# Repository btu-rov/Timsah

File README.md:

# Timsah
This is Open Source ROV project which is made by Bursa Technical University ROV Team.

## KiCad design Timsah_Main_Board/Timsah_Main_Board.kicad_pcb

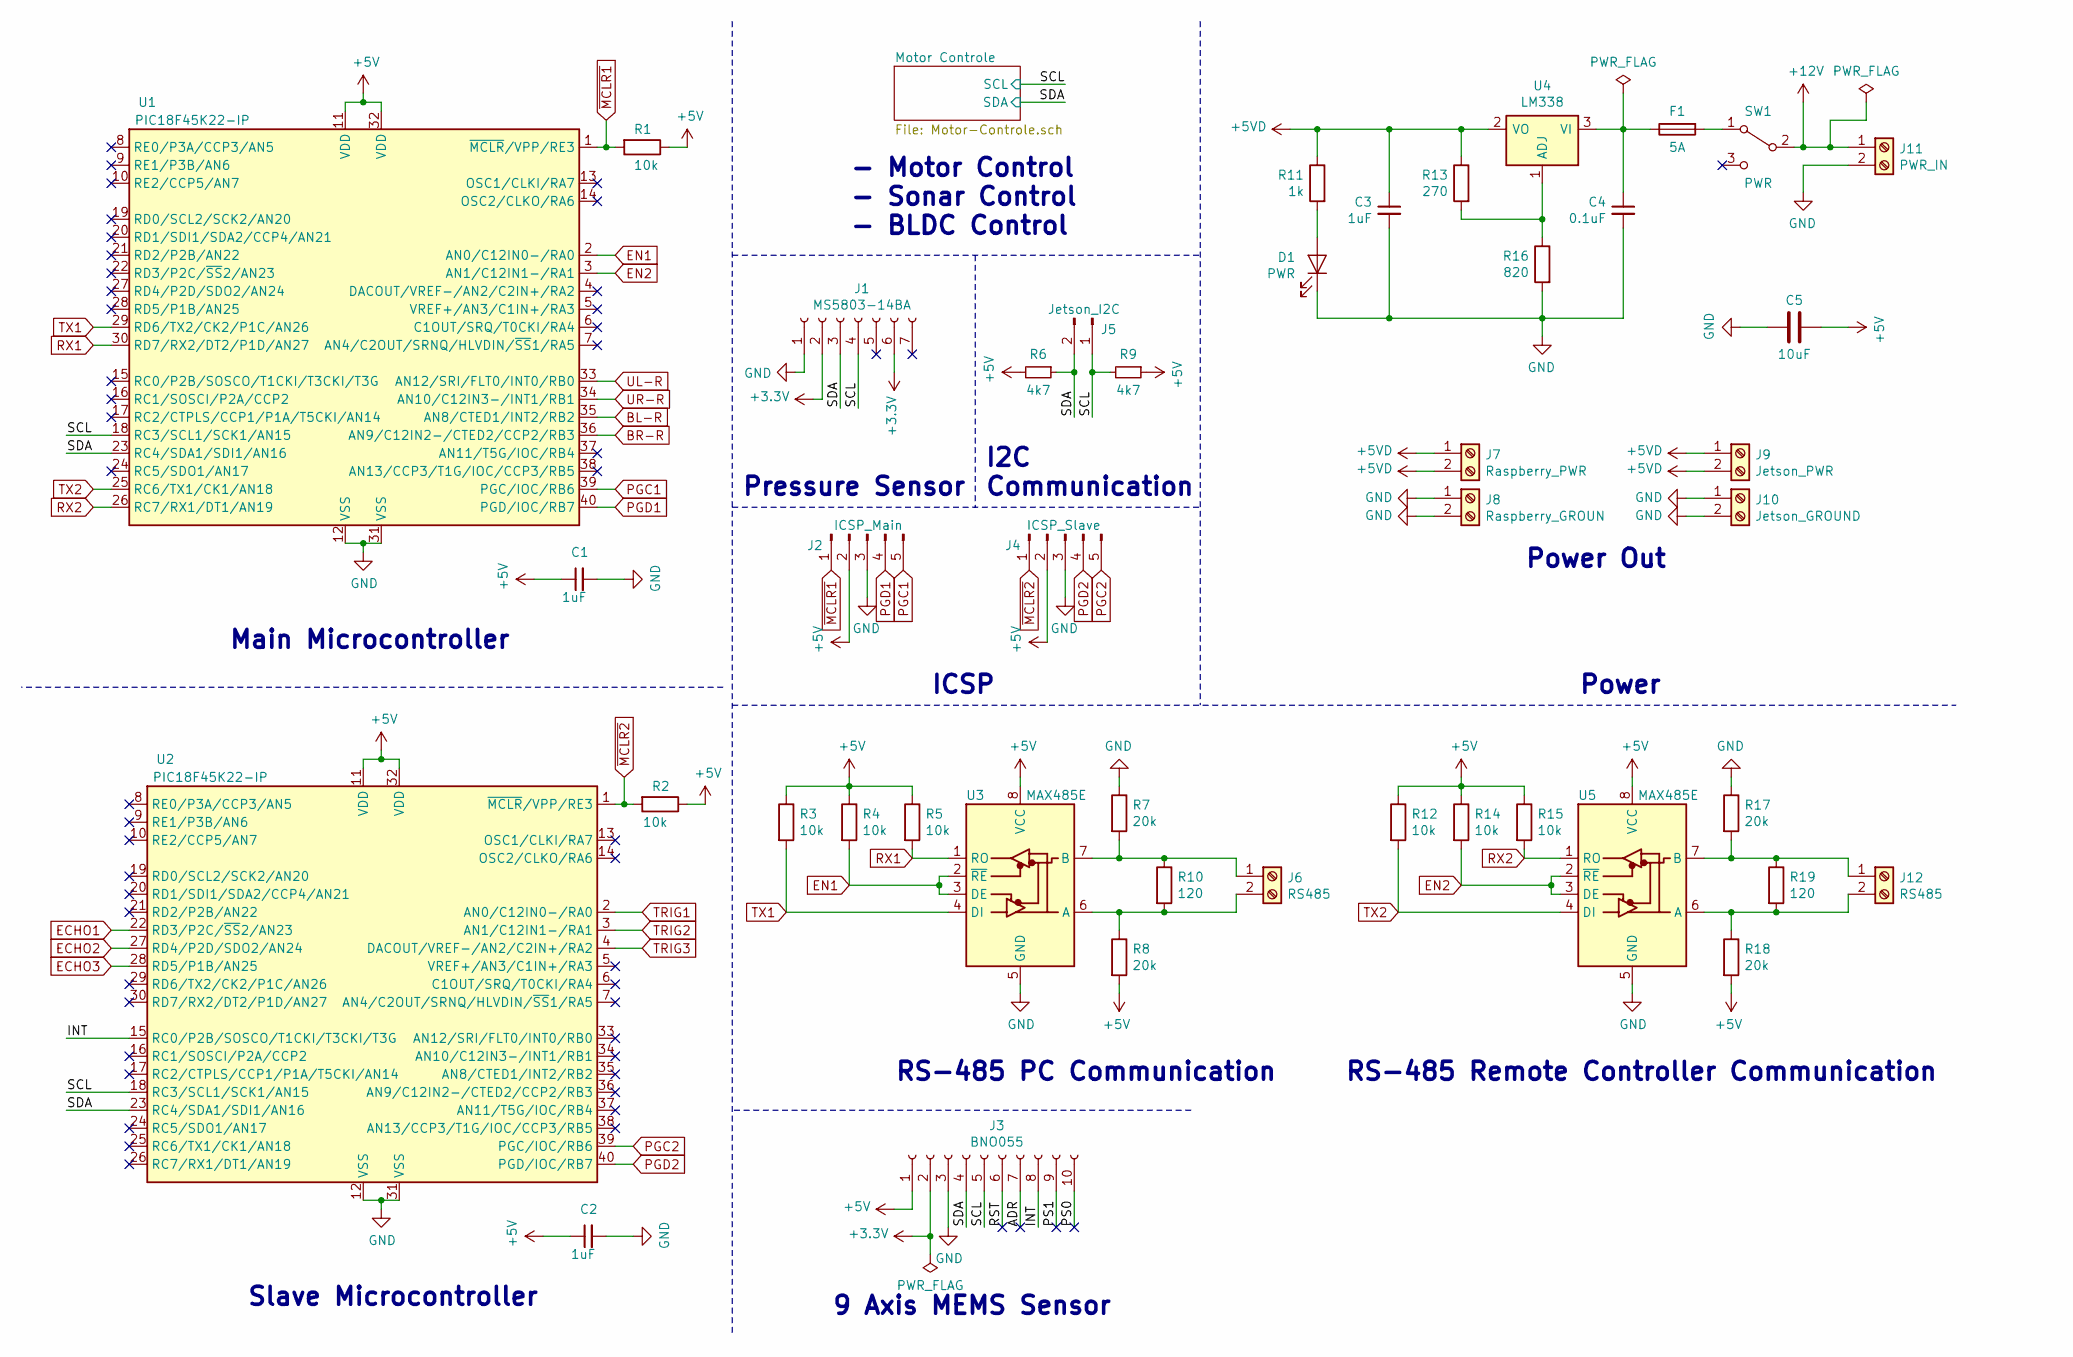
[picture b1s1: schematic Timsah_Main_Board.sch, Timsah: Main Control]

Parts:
C1, C2, C3: 1uF; C_0805_2012Metric_Pad1.15x1.40mm_HandSolder
C4: 0.1uF; C_0805_2012Metric_Pad1.15x1.40mm_HandSolder
C5: 10uF; C_0805_2012Metric_Pad1.15x1.40mm_HandSolder
D1: PWR; LED_0805_2012Metric_Pad1.15x1.40mm_HandSolder
F1: 5A; Fuseholder_23x9x10mm
J1: MS5803-14BA; PinSocket_1x07_P2.54mm_Vertical
J2: ICSP_Main; PinSocket_1x05_P2.54mm_Vertical
J3: BNO055; BNO055-Module_Adafruit
J4: ICSP_Slave; PinSocket_1x05_P2.54mm_Vertical
J5: Jetson_I2C; PinHeader_1x02_P2.54mm_Vertical
J6, J12: RS485; TerminalBlock_4Ucon_1x02_P3.50mm_Vertical
J7: Raspberry_PWR; TerminalBlock_4Ucon_1x02_P3.50mm_Vertical
J8: Raspberry_GROUN; TerminalBlock_4Ucon_1x02_P3.50mm_Vertical
J9: Jetson_PWR; TerminalBlock_4Ucon_1x02_P3.50mm_Vertical
J10: Jetson_GROUND; TerminalBlock_4Ucon_1x02_P3.50mm_Vertical
J11: PWR_IN; TerminalBlock_bornier-2_P5.08mm
R1, R2, R3, R4, R5, R12, R14, R15: 10k; R_0805_2012Metric_Pad1.15x1.40mm_HandSolder
R6, R9: 4k7; R_0805_2012Metric_Pad1.15x1.40mm_HandSolder
R7, R8, R17, R18: 20k; R_0805_2012Metric_Pad1.15x1.40mm_HandSolder
R10, R19: 120; R_Axial_DIN0207_L6.3mm_D2.5mm_P10.16mm_Horizontal
R11: 1k; R_0805_2012Metric_Pad1.15x1.40mm_HandSolder
R13: 270; R_Axial_DIN0207_L6.3mm_D2.5mm_P10.16mm_Horizontal
R16: 820; R_Axial_DIN0207_L6.3mm_D2.5mm_P10.16mm_Horizontal
SW1: PWR; SW_Slide_1P2T_0.105pitch
U1, U2: PIC18F45K22-IP; DIP-40_W15.24mm_Socket
U3, U5: MAX485E; DIP-8_W7.62mm_Socket
U4: LM338; TO-3

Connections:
+3V3: J1.2, J1.6, J3.2
+5VD: C3.1, J7.1, J7.2, J9.1, J9.2, R11.1, R13.1, U4.2 (VO)
+12V: J11.1, SW1.2 (B); also elsewhere on the board
/ADR: J3.7
/INT: J3.8, U2.15 (RC0/P2B/SOSCO/T1CKI/T3CKI/T3G)
/PS0: J3.10
/PS1: J3.9
/RST: J3.6
/SCL: J1.4, J3.5, J5.1, R9.2, U1.18 (RC3/SCL1/SCK1/AN15), U2.18 (RC3/SCL1/SCK1/AN15); also elsewhere on the board
/SDA: J1.3, J3.4, J5.2, R6.1, U1.23 (RC4/SDA1/SDI1/AN16), U2.23 (RC4/SDA1/SDI1/AN16); also elsewhere on the board
BEC: C1.1, C2.1, C5.1, J2.2, J3.1, J4.2, R1.1, R2.1, R3.1, R4.1, R5.1, R6.2, R8.2, R9.1, R12.1, R14.1, R15.1, R18.2, U1.11 (VDD), U1.32 (VDD), U2.11 (VDD), U2.32 (VDD), U3.8 (VCC), U5.8 (VCC); also elsewhere on the board
BL-R: U1.35 (AN8/CTED1/INT2/RB2); also elsewhere on the board
BR-R: U1.36 (AN9/C12IN2-/CTED2/CCP2/RB3); also elsewhere on the board
ECHO1: U2.22 (RD3/P2C/~SS~2/AN23); also elsewhere on the board
ECHO2: U2.27 (RD4/P2D/SDO2/AN24); also elsewhere on the board
ECHO3: U2.28 (RD5/P1B/AN25); also elsewhere on the board
EN1: R4.2, U1.2 (AN0/C12IN0-/RA0), U3.2 (~RE), U3.3 (DE)
EN2: R14.2, U1.3 (AN1/C12IN1-/RA1), U5.2 (~RE), U5.3 (DE)
GND: C1.2, C2.2, C3.2, C4.2, C5.2, D1.1 (K), J1.1, J2.3, J3.3, J4.3, J8.1, J8.2, J10.1, J10.2, J11.2, R7.1, R16.2, R17.1, U1.12 (VSS), U1.31 (VSS), U2.12 (VSS), U2.31 (VSS), U3.5 (GND), U5.5 (GND); also elsewhere on the board
unnamed: C4.1, F1.1, U4.3 (VI)
unnamed: D1.2 (A), R11.2
unnamed: F1.2, SW1.1 (A)
unnamed: J6.1, R7.2, R10.1, U3.7 (B)
unnamed: J6.2, R8.1, R10.2, U3.6 (A)
unnamed: J12.1, R17.2, R19.1, U5.7 (B)
unnamed: J12.2, R18.1, R19.2, U5.6 (A)
unnamed: R13.2, R16.1, U4.1 (ADJ)
PGC1: J2.5, U1.39 (PGC/IOC/RB6)
PGC2: J4.5, U2.39 (PGC/IOC/RB6)
PGD1: J2.4, U1.40 (PGD/IOC/RB7)
PGD2: J4.4, U2.40 (PGD/IOC/RB7)
RX1: R5.2, U1.30 (RD7/RX2/DT2/P1D/AN27), U3.1 (RO)
RX2: R15.2, U1.26 (RC7/RX1/DT1/AN19), U5.1 (RO)
TRIG1: U2.2 (AN0/C12IN0-/RA0); also elsewhere on the board
TRIG2: U2.3 (AN1/C12IN1-/RA1); also elsewhere on the board
TRIG3: U2.4 (DACOUT/VREF-/AN2/C2IN+/RA2); also elsewhere on the board
TX1: R3.2, U1.29 (RD6/TX2/CK2/P1C/AN26), U3.4 (DI)
TX2: R12.2, U1.25 (RC6/TX1/CK1/AN18), U5.4 (DI)
UL-R: U1.33 (AN12/SRI/FLT0/INT0/RB0); also elsewhere on the board
UR-R: U1.34 (AN10/C12IN3-/INT1/RB1); also elsewhere on the board
~MCLR1: J2.1, R1.2, U1.1 (~MCLR~/VPP/RE3)
~MCLR2: J4.1, R2.2, U2.1 (~MCLR~/VPP/RE3)

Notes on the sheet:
Power
9 Axis MEMS Sensor
RS-485 Remote Controller Communication
Slave Microcontroller
Main Microcontroller
Pressure Sensor
ICSP
Power Out
I2C Communication
RS-485 PC Communication
- Motor Control - Sonar Control - BLDC Control

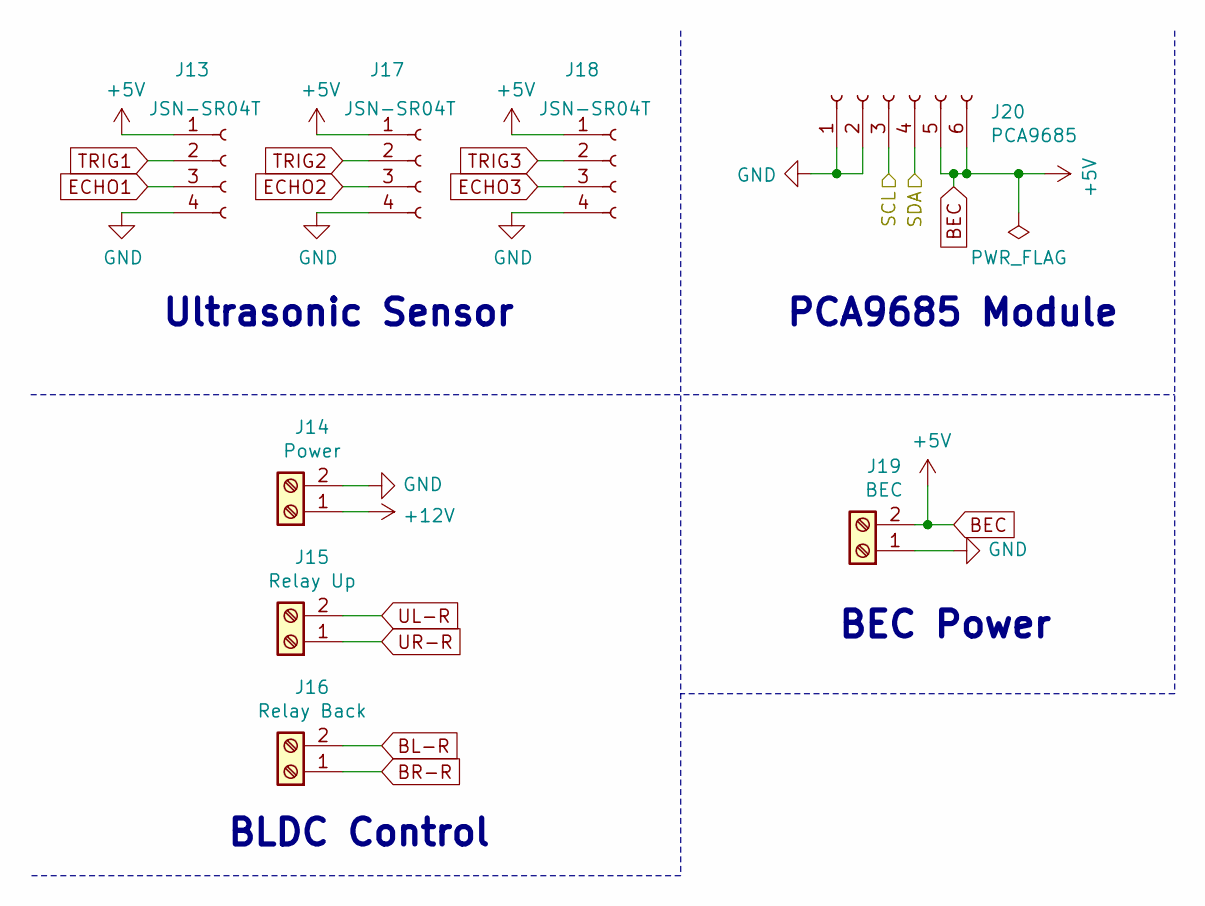
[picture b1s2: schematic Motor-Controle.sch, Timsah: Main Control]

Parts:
J13, J17, J18: JSN-SR04T; PinSocket_1x04_P2.54mm_Vertical
J14: Power; TerminalBlock_bornier-2_P5.08mm
J15: Relay Up; PinSocket_1x02_P2.54mm_Vertical
J16: Relay Back; PinSocket_1x02_P2.54mm_Vertical
J19: BEC; TerminalBlock_4Ucon_1x02_P3.50mm_Vertical
J20: PCA9685; PinSocket_1x06_P2.54mm_Vertical

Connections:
+12V: J14.1; also elsewhere on the board
/SCL: J20.3; also elsewhere on the board
/SDA: J20.4; also elsewhere on the board
BEC: J13.1, J17.1, J18.1, J19.2, J20.5, J20.6; also elsewhere on the board
BL-R: J16.2; also elsewhere on the board
BR-R: J16.1; also elsewhere on the board
ECHO1: J13.3; also elsewhere on the board
ECHO2: J17.3; also elsewhere on the board
ECHO3: J18.3; also elsewhere on the board
GND: J13.4, J14.2, J17.4, J18.4, J19.1, J20.1, J20.2; also elsewhere on the board
TRIG1: J13.2; also elsewhere on the board
TRIG2: J17.2; also elsewhere on the board
TRIG3: J18.2; also elsewhere on the board
UL-R: J15.2; also elsewhere on the board
UR-R: J15.1; also elsewhere on the board

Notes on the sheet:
BLDC Control
Ultrasonic Sensor
PCA9685 Module
BEC Power

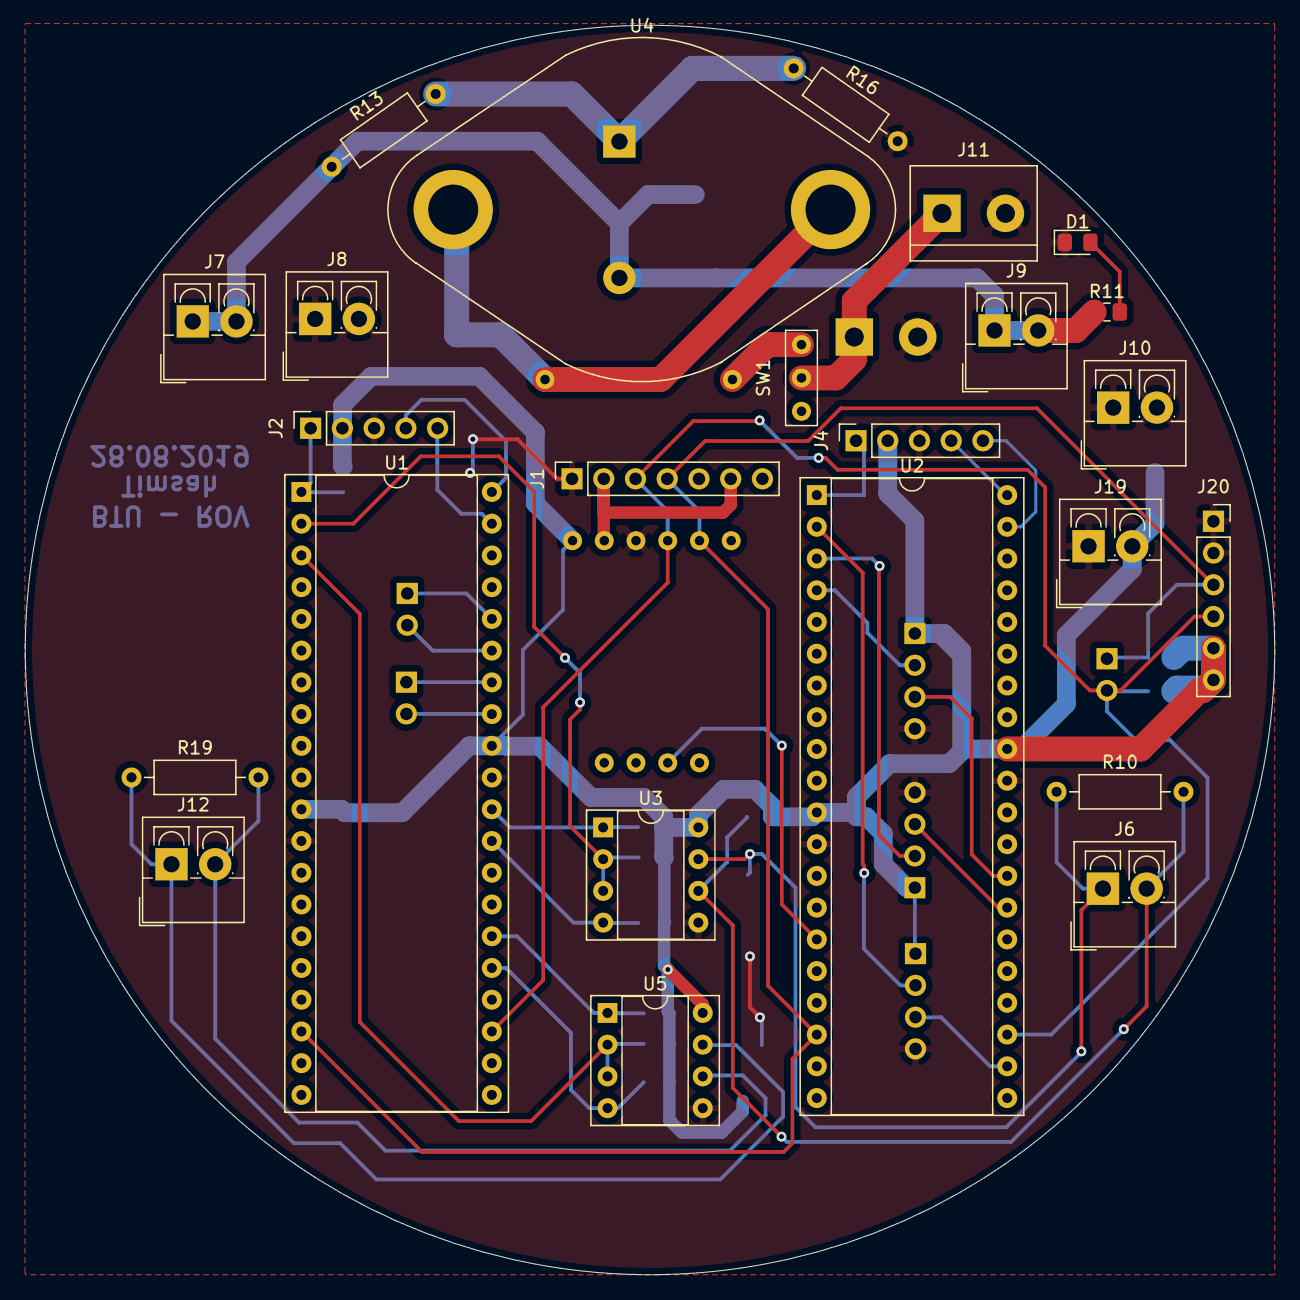
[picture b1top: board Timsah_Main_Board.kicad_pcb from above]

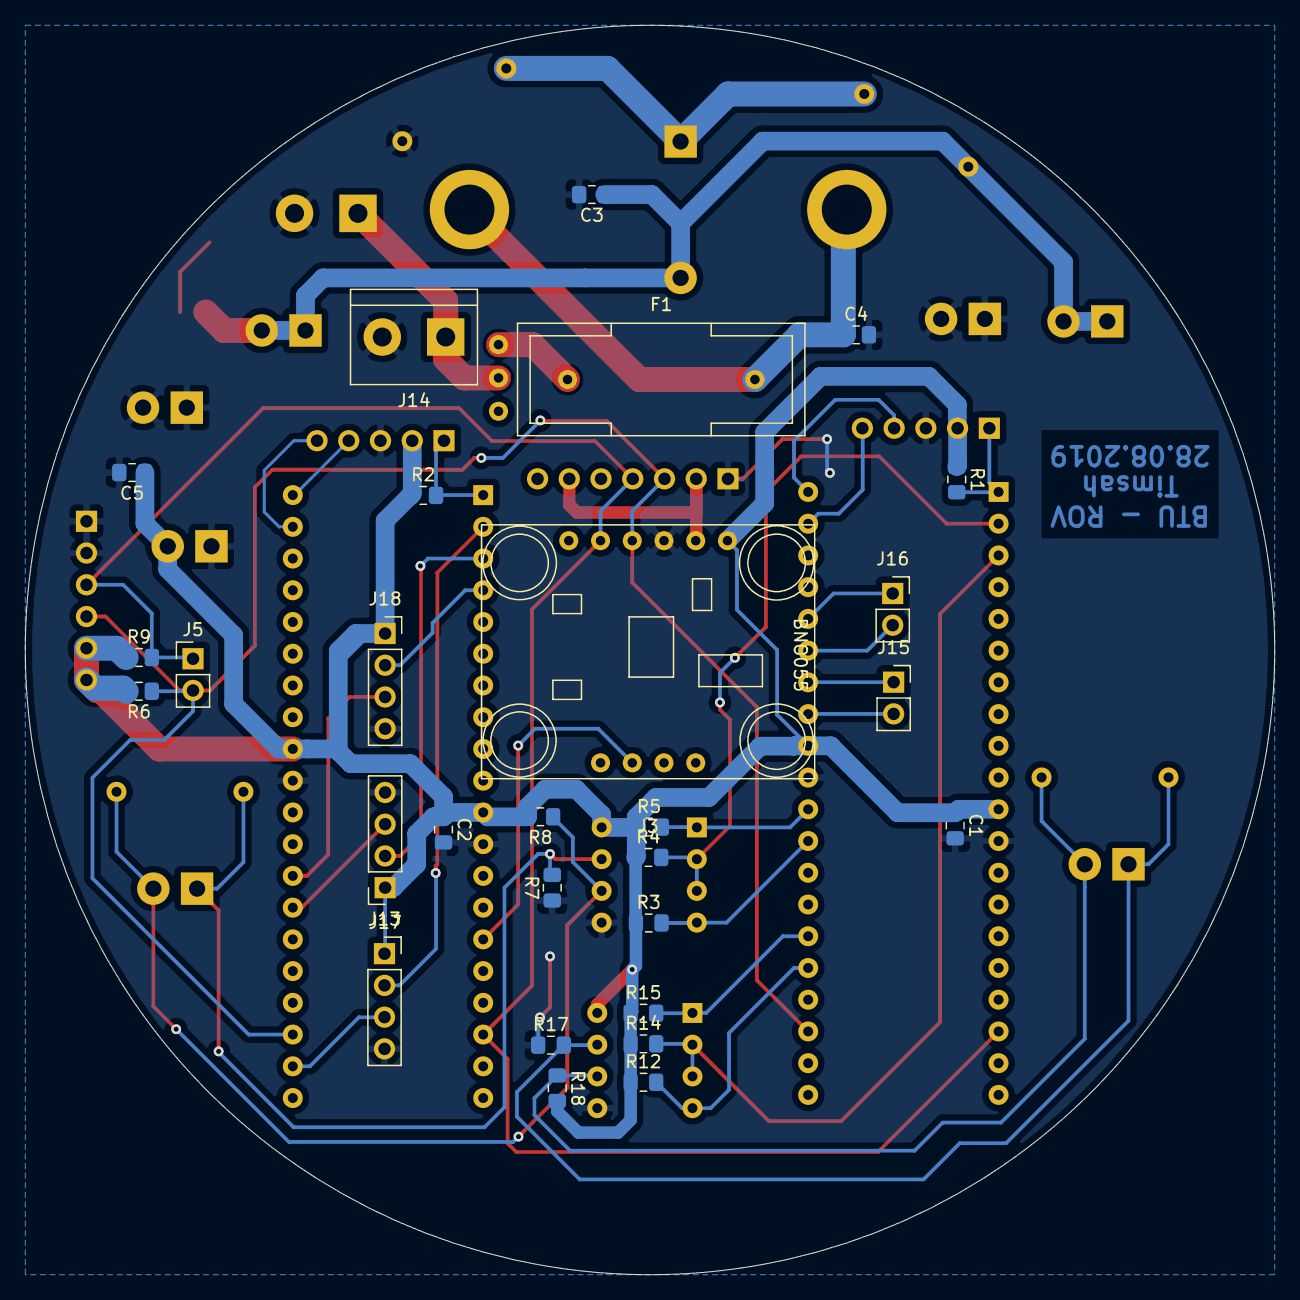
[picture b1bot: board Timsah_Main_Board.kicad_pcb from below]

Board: 2 copper layers, 100.0 x 100.0 mm, 52 parts (28 on the bottom side), 38 nets.

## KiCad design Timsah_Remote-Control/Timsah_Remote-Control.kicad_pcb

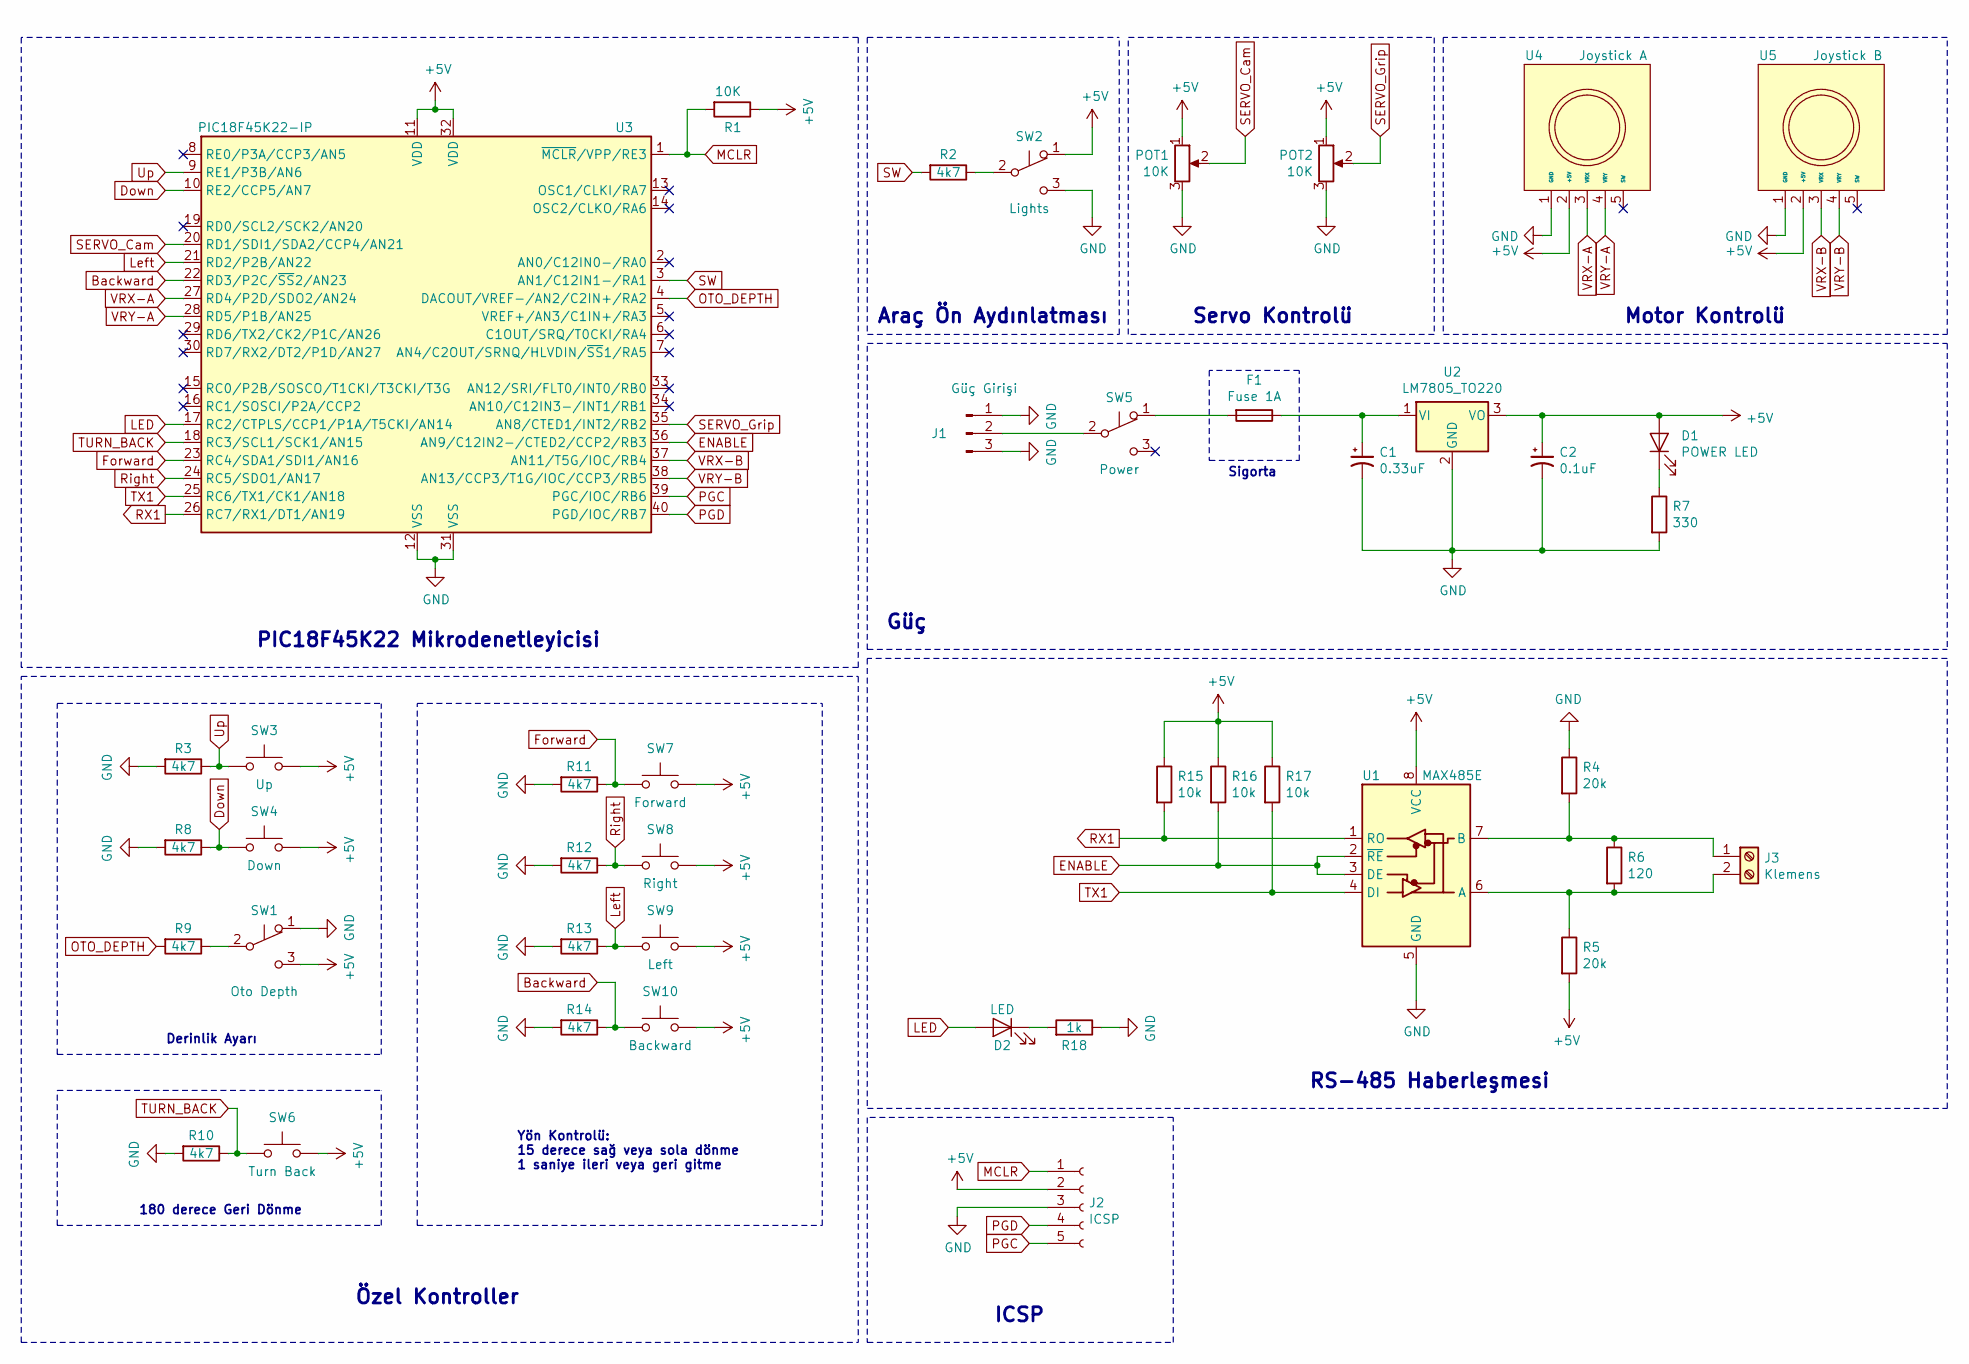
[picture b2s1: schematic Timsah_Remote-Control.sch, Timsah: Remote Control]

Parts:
C1: 0.33uF; C_Radial_D5.0mm_H7.0mm_P2.00mm
C2: 0.1uF; C_Radial_D5.0mm_H7.0mm_P2.00mm
D1: POWER LED; LED_D5.0mm
D2: LED; LED_D5.0mm
F1: Fuse 1A; Fuseholder_23x9x10mm
J1: Güç Girişi; PinHeader_1x03_P2.54mm_Vertical
J2: ICSP; PinHeader_1x05_P2.54mm_Vertical
J3: Klemens; TerminalBlock_4Ucon_1x02_P3.50mm_Vertical
POT1, POT2: 10K; Potentiometer_Lineer-B503
R1: 10K; R_Axial_DIN0207_L6.3mm_D2.5mm_P10.16mm_Horizontal
R2, R3, R8, R9, R10, R11, R12, R13, R14: 4k7; R_Axial_DIN0207_L6.3mm_D2.5mm_P10.16mm_Horizontal
R4, R5: 20k; R_Axial_DIN0207_L6.3mm_D2.5mm_P10.16mm_Horizontal
R6: 120; R_Axial_DIN0207_L6.3mm_D2.5mm_P10.16mm_Horizontal
R7: 330; R_Axial_DIN0207_L6.3mm_D2.5mm_P10.16mm_Horizontal
R15, R16, R17: 10k; R_Axial_DIN0207_L6.3mm_D2.5mm_P10.16mm_Horizontal
R18: 1k; R_Axial_DIN0207_L6.3mm_D2.5mm_P10.16mm_Horizontal
SW1: Oto Depth; SW_Slide_1P2T_0.105pitch
SW2: Lights; SW_Slide_1P2T_0.105pitch
SW3: Up; SW_PUSH_6mm_H5mm
SW4: Down; SW_PUSH_6mm_H5mm
SW5: Power; SW_Slide_1P2T_0.105pitch
SW6: Turn Back; SW_PUSH_6mm_H5mm
SW7: Forward; SW_PUSH_6mm_H5mm
SW8: Right; SW_PUSH_6mm_H5mm
SW9: Left; SW_PUSH_6mm_H5mm
SW10: Backward; SW_PUSH_6mm_H5mm
U1: MAX485E; DIP-8_W7.62mm_Socket
U2: LM7805_TO220; TO-220-3_Vertical
U3: PIC18F45K22-IP; DIP-40_W15.24mm_Socket
U4: Joystick A; Joystick
U5: Joystick B; Joystick

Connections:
+5V: C2.1, D1.2 (A), J2.2, POT1.1, POT2.1, R1.1, R5.2, R15.1, R16.1, R17.1, SW1.3 (C), SW2.1 (A), SW3.2, SW4.2, SW6.2, SW7.2, SW8.2, SW9.2, SW10.2, U1.8 (VCC), U2.3 (VO), U3.11 (VDD), U3.32 (VDD), U4.2 (+5V), U5.2 (+5V)
Backward: R14.1, SW10.1, U3.22 (RD3/P2C/~SS~2/AN23)
Down: R8.1, SW4.1, U3.10 (RE2/CCP5/AN7)
ENABLE: R16.2, U1.2 (~RE), U1.3 (DE), U3.36 (AN9/C12IN2-/CTED2/CCP2/RB3)
Forward: R11.1, SW7.1, U3.23 (RC4/SDA1/SDI1/AN16)
GND: C1.2, C2.2, J1.1, J1.3, J2.3, POT1.3, POT2.3, R3.2, R4.1, R7.2, R8.2, R10.2, R11.2, R12.2, R13.2, R14.2, R18.1, SW1.1 (A), SW2.3 (C), U1.5 (GND), U2.2 (GND), U3.12 (VSS), U3.31 (VSS), U4.1 (GND), U5.1 (GND)
LED: D2.2 (A), U3.17 (RC2/CTPLS/CCP1/P1A/T5CKI/AN14)
Left: R13.1, SW9.1, U3.21 (RD2/P2B/AN22)
MCLR: J2.1, R1.2, U3.1 (~MCLR~/VPP/RE3)
unnamed: C1.1, F1.1, U2.1 (VI)
unnamed: D1.1 (K), R7.1
unnamed: D2.1 (K), R18.2
unnamed: F1.2, SW5.1 (A)
unnamed: J1.2, SW5.2 (B)
unnamed: J3.1, R4.2, R6.1, U1.7 (B)
unnamed: J3.2, R5.1, R6.2, U1.6 (A)
unnamed: R2.1, SW2.2 (B)
unnamed: R9.1, SW1.2 (B)
OTO_DEPTH: R9.2, U3.4 (DACOUT/VREF-/AN2/C2IN+/RA2)
PGC: J2.5, U3.39 (PGC/IOC/RB6)
PGD: J2.4, U3.40 (PGD/IOC/RB7)
RX1: R15.2, U1.1 (RO), U3.26 (RC7/RX1/DT1/AN19)
Right: R12.1, SW8.1, U3.24 (RC5/SDO1/AN17)
SERVO_Cam: POT1.2, U3.20 (RD1/SDI1/SDA2/CCP4/AN21)
SERVO_Grip: POT2.2, U3.35 (AN8/CTED1/INT2/RB2)
SW: R2.2, U3.3 (AN1/C12IN1-/RA1)
TURN_BACK: R10.1, SW6.1, U3.18 (RC3/SCL1/SCK1/AN15)
TX1: R17.2, U1.4 (DI), U3.25 (RC6/TX1/CK1/AN18)
Up: R3.1, SW3.1, U3.9 (RE1/P3B/AN6)
VRX-A: U3.27 (RD4/P2D/SDO2/AN24), U4.3 (VRX)
VRX-B: U3.37 (AN11/T5G/IOC/RB4), U5.3 (VRX)
VRY-A: U3.28 (RD5/P1B/AN25), U4.4 (VRY)
VRY-B: U3.38 (AN13/CCP3/T1G/IOC/CCP3/RB5), U5.4 (VRY)

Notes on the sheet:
Motor Kontrolü
Servo Kontrolü
Araç Ön Aydınlatması
Güç
RS-485 Haberleşmesi
ICSP
PIC18F45K22 Mikrodenetleyicisi
Sigorta
Derinlik Ayarı
180 derece Geri Dönme
Yön Kontrolü: 15 derece sağ veya sola dönme 1 saniye ileri veya geri gitme
Özel Kontroller

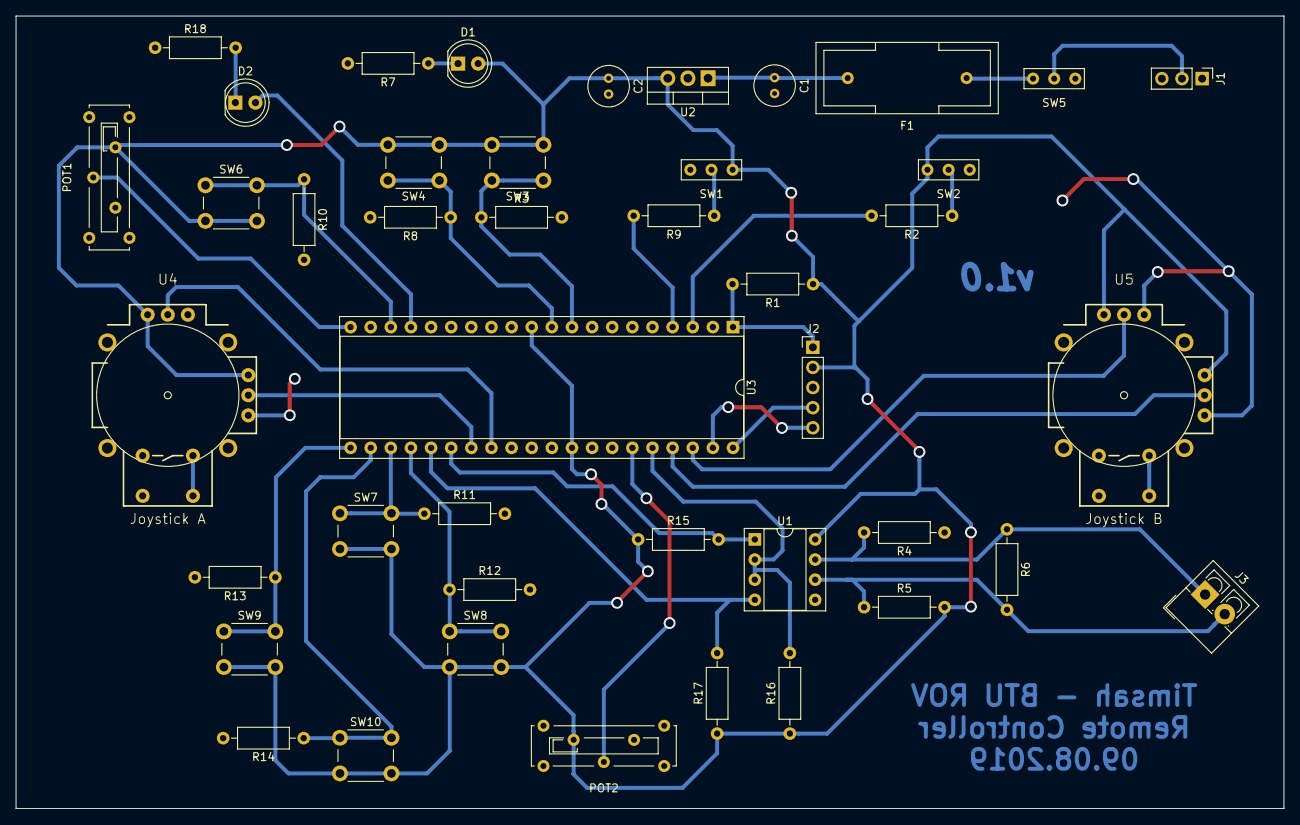
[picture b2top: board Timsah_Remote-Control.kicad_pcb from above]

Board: 2 copper layers, 160.0 x 100.0 mm, 43 parts (0 on the bottom side), 33 nets.

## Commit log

2019-03-24 Timsah GUI initialize.
2019-03-24 Data read protocol initialization.
2019-03-24 Added .gitignore and lock files.
2019-03-25 GUI changed to ElectronJS.
2019-03-25 Update arduino test code.
    Added changin tmp value.
2019-03-25 ElectronJS initialization with data receive protocol.
2019-03-25 File name changed.
2019-03-28 Added send data function.
2019-04-19 Changed files locations.
2019-04-19 Create LICENSE
2019-04-19 Update GUI.
    - Added graphs with GraphJS.
    - Added Bootstrap.
2019-04-20 Added speed graphs.
    - Added SpeedX and SpeedY graphs.
    - Added Graph's labels.
    - Color changes.
    - Temperature graph min and max changes.
2019-04-21 Added new dadas to send.
2019-04-21 Maximize window when starting.
2019-04-21 Changed oriantation and added new datas.
2019-04-21 Update index.js
    - Visualize random datas.
    - Added speed and sonar datas.
    - Added rendering charts.
2019-04-21 Initialize Schematic
2019-04-21 Remote controller schematic update.
    - Some titels fixed
    - Microcontroller updated
    - Project library edited
    - Some oriantations changed
2019-04-23 Added special controls.
2019-04-23 Added schematic pdf.
2019-04-23 Added motor speed, tilt and sonar datas.
2019-04-23 GUI updated.
    - Added motor speeds
    - Added tilt graph
    - Added sonar graphs
    - Changed colors
2019-04-24 Initialize Main Board
2019-04-25 Initialize
2019-04-25 Deleted
2019-04-25 Schema update.
2019-04-26 Blok Diagram update
2019-04-27 Update block diagram.
2019-04-27 Update Main Board.
2019-05-02 Schematic Update
2019-05-17 Added main body that is assembled with other parts
2019-05-17 Added other parts.
2019-05-17 Added PNG files.
2019-07-15 Updated ISS_Blok_Diagram.pdf
2019-07-15 Updated ISS_Blok_Diagram.png
2019-07-15 Update schematics.
2019-07-15 Added new schemas.
2019-07-24 Schematic updates.
2019-07-26 Remote update.
    - PCB design started.
2019-08-01 Added software.
2019-08-01 File reorganisations.
2019-08-04 I2C Update.
    - Fixed i2c read
    - Added BNO055 setup library.
2019-08-05 v1.0 of libraries.
    - Added cmbus protochol.
    - Some small changes.
2019-08-06 Added vehicle controle protocol.
2019-08-08 Added remote controle PCB design.
2019-08-08 Remote control board recreated.
2019-08-08 Remote controller joystick pins changed.
    Joystick A pins do not connected to analog pins.
2019-08-08 Changed io pins.
2019-08-28 Hardware Update
2019-08-28 Update PCB
2020-07-07 Bump electron from 5.0.8 to 7.2.4 in /TimsahGUI/ElectronJS
    Bumps [electron](https://github.com/electron/electron) from 5.0.8 to 7.2.4.
    - [Release notes](https://github.com/electron/electron/releases)
    - [Changelog](https://github.com/electron/electron/blob/master/docs/breaking-changes.md)
    - [Commits](https://github.com/electron/electron/compare/v5.0.8...v7.2.4)
2020-09-09 Bump yargs-parser from 13.1.1 to 13.1.2 in /TimsahGUI/ElectronJS
    Bumps [yargs-parser](https://github.com/yargs/yargs-parser) from 13.1.1 to 13.1.2.
    - [Release notes](https://github.com/yargs/yargs-parser/releases)
    - [Changelog](https://github.com/yargs/yargs-parser/blob/master/docs/CHANGELOG-full.md)
    - [Commits](https://github.com/yargs/yargs-parser/commits)
2020-12-11 Bump ini from 1.3.5 to 1.3.7 in /TimsahGUI/ElectronJS
    Bumps [ini](https://github.com/isaacs/ini) from 1.3.5 to 1.3.7.
    - [Release notes](https://github.com/isaacs/ini/releases)
    - [Commits](https://github.com/isaacs/ini/compare/v1.3.5...v1.3.7)
2021-01-28 Bump electron from 5.0.8 to 9.4.0 in /TimsahGUI/ElectronJS
    Bumps [electron](https://github.com/electron/electron) from 5.0.8 to 9.4.0.
    - [Release notes](https://github.com/electron/electron/releases)
    - [Changelog](https://github.com/electron/electron/blob/master/docs/breaking-changes.md)
    - [Commits](https://github.com/electron/electron/compare/v5.0.8...v9.4.0)

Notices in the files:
Timsah_Main_Board/Motor-Controle.sch:
https://creativecommons.org/licenses/by-sa/4.0
Released under the Creative Commons
